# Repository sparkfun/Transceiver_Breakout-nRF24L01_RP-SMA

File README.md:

SparkFun Transceiver Breakout - nRF24L01+ (RP-SMA)
========================================

[*SparkFun Transceiver Breakout - nRF24L01+ (RP-SMA) (WRL-00705)*](https://www.sparkfun.com/products/705)

This module uses the 2.4GHz transceiver from Nordic Semiconductor, the nRF24L01+. 
This board features a reverse polarized SMA connector for maximum RF range.

Repository Contents
-------------------

* **/Hardware** - Eagle design files (.brd, .sch)
* **/Production** - Production panel files (.brd)

Documentation
--------------
* **[Hookup Guide](https://learn.sparkfun.com/tutorials/nrf24l01-transceiver-hookup-guide)** - Basic hookup guide.
* **[SparkFun Fritzing repo](https://github.com/sparkfun/Fritzing_Parts)** - Fritzing diagrams for SparkFun products.
* **[SparkFun 3D Model repo](https://github.com/sparkfun/3D_Models)** - 3D models of SparkFun products. 

License Information
-------------------
This product is _**open source**_! 

The **hardware** is released under [Creative Commons ShareAlike 4.0 International](https://creativecommons.org/licenses/by-sa/4.0/).

Please use, reuse, and modify these files as you see fit. Please maintain attribution to SparkFun Electronics and release anything derivative under the same license.

Distributed as-is; no warranty is given.

- Your friends at SparkFun.

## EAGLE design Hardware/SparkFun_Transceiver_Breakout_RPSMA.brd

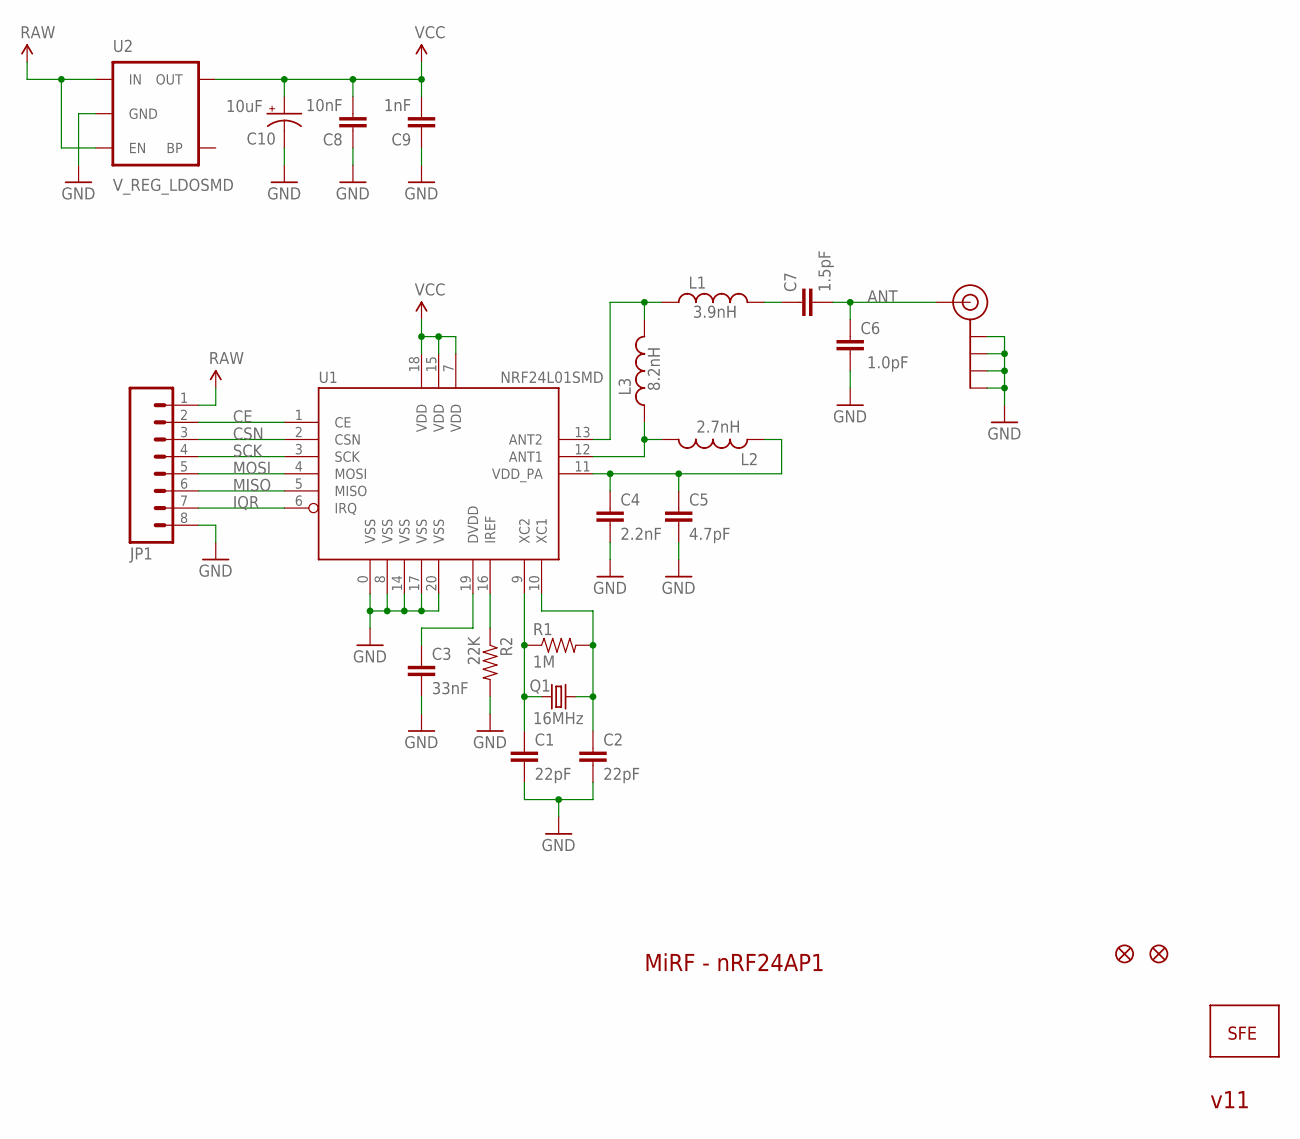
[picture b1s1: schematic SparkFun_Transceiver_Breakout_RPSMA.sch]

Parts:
C1, C2: 22pF; C0402
C3: 33nF; C0402
C4: 2.2nF; C0402
C5: 4.7pF; C0402
C6: 1.0pF; C0402
C7: 1.5pF; C0402
C8: 10nF; C0402
C9: 1nF; C0402
C10: 10uF; EIA3216
FID1, FID2: FIDUCIALUFIDUCIAL; MICRO-FIDUCIAL
J$1: SMA_EDGE; SMA-EDGE
JP1: M08; 1X08
L1: 3.9nH; C0402
L2: 2.7nH; C0402
L3: 8.2nH; C0402
Q1: 16MHz; CRYSTAL-SMD-5X3
R1: 1M; C0402
R2: 22K; C0402
U1: NRF24L01SMD; QFN20
U2: V_REG_LDOSMD; SOT23-5
U$5: LOGO-SFENEW; SFE-NEW-WEBLOGO

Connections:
ANT: C6.2, C7.2, J$1.SIG (SIGNAL)
CE: JP1.2, U1.1 (CE)
CSN: JP1.3, U1.2 (CSN)
GND: C1.2, C2.2, C3.2, C4.2, C5.2, C6.1, C8.1, C9.1, C10.C (-), J$1.GND@0 (GND), J$1.GND@1 (GND), J$1.GND@2 (GND), J$1.GND@3 (GND), JP1.8, R2.2, U1.0 (VSS), U1.8 (VSS), U1.14 (VSS), U1.17 (VSS), U1.20 (VSS), U2.2 (GND)
IQR: JP1.7, U1.6 (IRQ)
MISO: JP1.6, U1.5 (MISO)
MOSI: JP1.5, U1.4 (MOSI)
unnamed: C1.1, Q1.1, R1.1, U1.9 (XC2)
unnamed: C2.1, Q1.3 (2), R1.2, U1.10 (XC1)
unnamed: L2.2, L3.1, U1.12 (ANT1)
unnamed: R2.1, U1.16 (IREF)
unnamed: C3.1, U1.19 (DVDD)
unnamed: L1.1, L3.2, U1.13 (ANT2)
unnamed: C4.1, C5.1, L2.1, U1.11 (VDD_PA)
unnamed: C7.1, L1.2
RAW: JP1.1, U2.1 (IN), U2.3 (EN)
SCK: JP1.4, U1.3 (SCK)
VCC: C8.2, C9.2, C10.A (+), U1.7 (VDD), U1.15 (VDD), U1.18 (VDD), U2.5 (OUT)

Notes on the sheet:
MiRF - nRF24AP1
v11

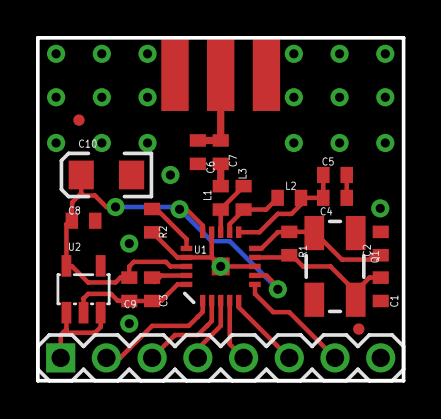
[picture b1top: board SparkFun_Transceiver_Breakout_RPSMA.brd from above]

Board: 2 copper layers, 20.3 x 19.1 mm, 23 parts (1 on the bottom side), 18 nets.

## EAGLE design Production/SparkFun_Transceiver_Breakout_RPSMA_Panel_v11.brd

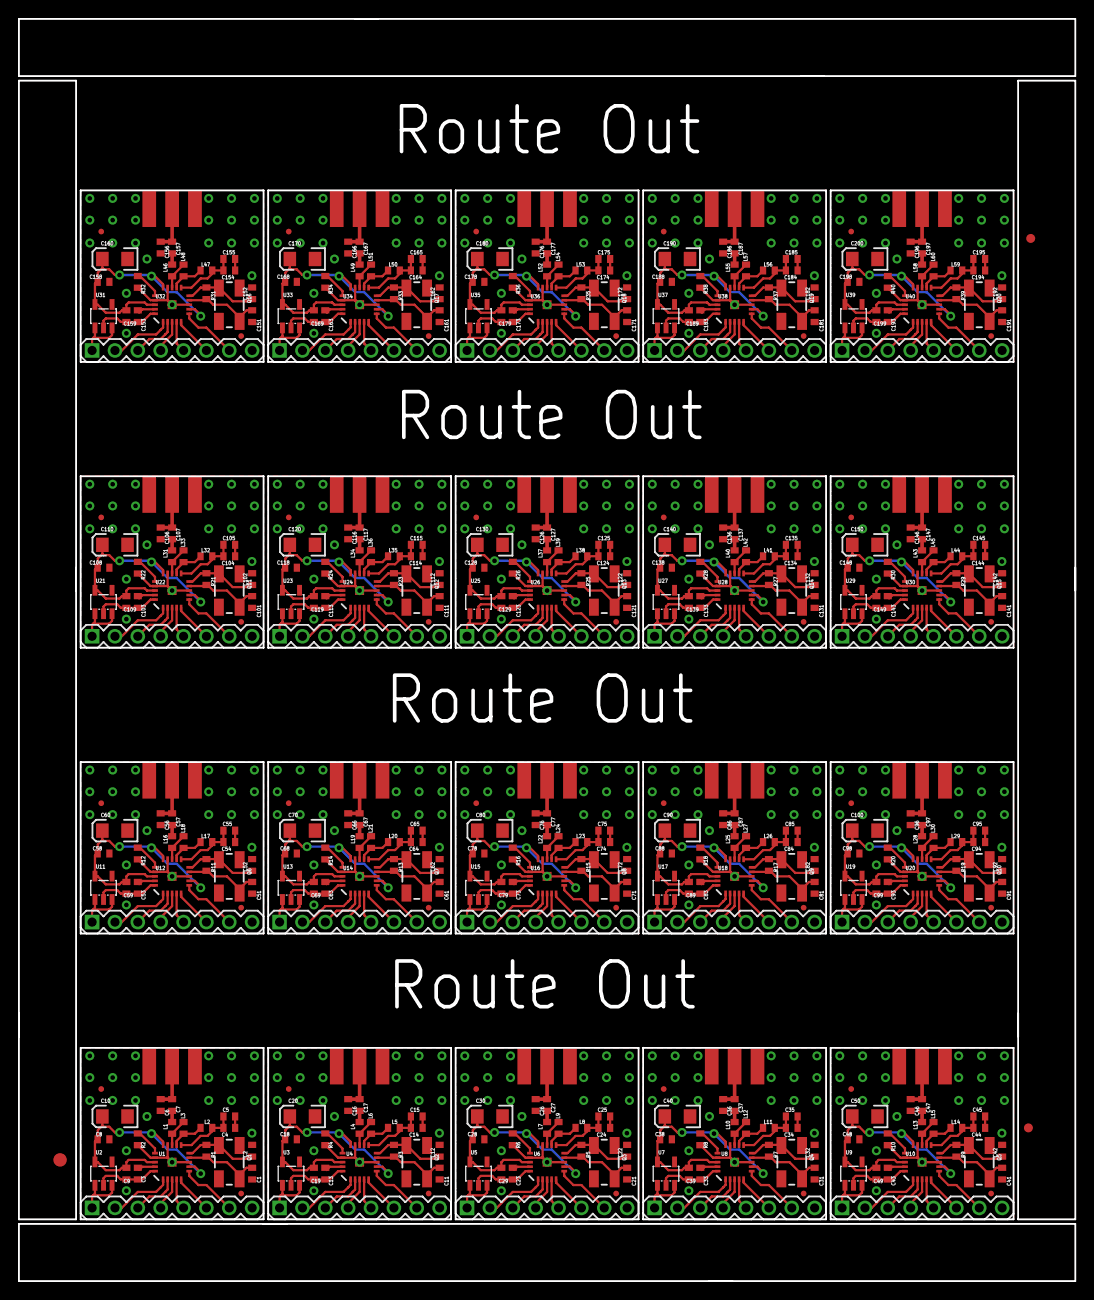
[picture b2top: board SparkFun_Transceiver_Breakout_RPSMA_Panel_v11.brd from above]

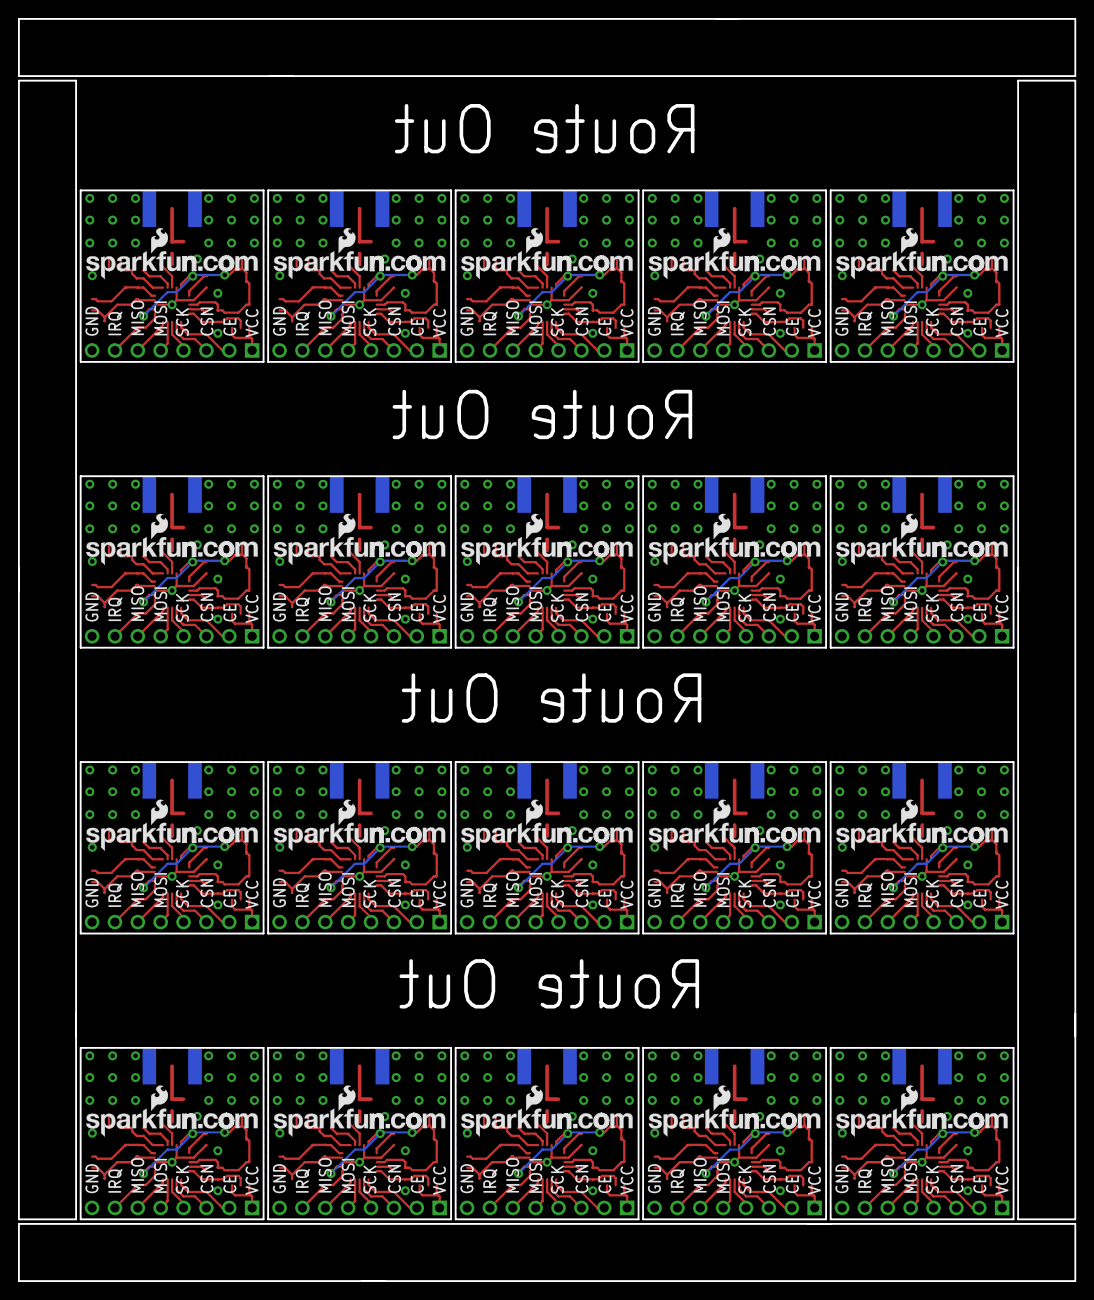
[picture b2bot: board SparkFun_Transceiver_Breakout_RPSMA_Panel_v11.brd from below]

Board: 2 copper layers, 117.3 x 140.2 mm, 463 parts (20 on the bottom side), 360 nets.

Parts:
C1, C2, C11, C12, C21, C22, C31, C32, C41, C42, C51, C52, C61, C62, C71, C72, C81, C82, C91, C92, C101, C102, C111, C112, C121, C122, C131, C132, C141, C142, C151, C152, C161, C162, C171, C172, C181, C182, C191, C192: 22pF; C0402
C3, C13, C23, C33, C43, C53, C63, C73, C83, C93, C103, C113, C123, C133, C143, C153, C163, C173, C183, C193: 33nF; C0402
C4, C14, C24, C34, C44, C54, C64, C74, C84, C94, C104, C114, C124, C134, C144, C154, C164, C174, C184, C194: 2.2nF; C0402
C5, C15, C25, C35, C45, C55, C65, C75, C85, C95, C105, C115, C125, C135, C145, C155, C165, C175, C185, C195: 4.7pF; C0402
C6, C16, C26, C36, C46, C56, C66, C76, C86, C96, C106, C116, C126, C136, C146, C156, C166, C176, C186, C196: 1.0pF; C0402
C7, C17, C27, C37, C47, C57, C67, C77, C87, C97, C107, C117, C127, C137, C147, C157, C167, C177, C187, C197: 1.5pF; C0402
C8, C18, C28, C38, C48, C58, C68, C78, C88, C98, C108, C118, C128, C138, C148, C158, C168, C178, C188, C198: 10nF; C0402
C9, C19, C29, C39, C49, C59, C69, C79, C89, C99, C109, C119, C129, C139, C149, C159, C169, C179, C189, C199: 1nF; C0402
C10, C20, C30, C40, C50, C60, C70, C80, C90, C100, C110, C120, C130, C140, C150, C160, C170, C180, C190, C200: 10uF; EIA3216
E$1: FIDUCIAL-1.5X3
E$5, E$6: FIDUCIAL-1X2
FID1, FID2, FID3, FID4, FID5, FID6, FID7, FID8, FID9, FID10, FID11, FID12, FID13, FID14, FID15, FID16, FID17, FID18, FID19, FID20, FID21, FID22, FID23, FID24, FID25, FID26, FID27, FID28, FID29, FID30, FID31, FID32, FID33, FID34, FID35, FID36, FID37, FID38, FID39, FID40: FIDUCIALUFIDUCIAL; MICRO-FIDUCIAL
J$1, J$2, J$3, J$4, J$5, J$6, J$7, J$8, J$9, J$10, J$11, J$12, J$13, J$14, J$15, J$16, J$17, J$18, J$19, J$20: SMA_EDGE; SMA-EDGE
JP1, JP2, JP3, JP4, JP5, JP6, JP7, JP8, JP9, JP10, JP11, JP12, JP13, JP14, JP15, JP16, JP17, JP18, JP19, JP20: 1X08
L1, L4, L7, L10, L13, L16, L19, L22, L25, L28, L31, L34, L37, L40, L43, L46, L49, L52, L55, L58: 3.9nH; C0402
L2, L5, L8, L11, L14, L17, L20, L23, L26, L29, L32, L35, L38, L41, L44, L47, L50, L53, L56, L59: 2.7nH; C0402
L3, L6, L9, L12, L15, L18, L21, L24, L27, L30, L33, L36, L39, L42, L45, L48, L51, L54, L57, L60: 8.2nH; C0402
Q1, Q2, Q3, Q4, Q5, Q6, Q7, Q8, Q9, Q10, Q11, Q12, Q13, Q14, Q15, Q16, Q17, Q18, Q19, Q20: 16MHz; CRYSTAL-SMD-5X3
R1, R3, R5, R7, R9, R11, R13, R15, R17, R19, R21, R23, R25, R27, R29, R31, R33, R35, R37, R39: 1M; C0402
R2, R4, R6, R8, R10, R12, R14, R16, R18, R20, R22, R24, R26, R28, R30, R32, R34, R36, R38, R40: 22K; C0402
U1, U4, U6, U8, U10, U12, U14, U16, U18, U20, U22, U24, U26, U28, U30, U32, U34, U36, U38, U40: NRF24L01SMD; QFN20
U2, U3, U5, U7, U9, U11, U13, U15, U17, U19, U21, U23, U25, U27, U29, U31, U33, U35, U37, U39: V_REG_LDOSMD; SOT23-5
U$1, U$2, U$3, U$4, U$5, U$6, U$7, U$8, U$9, U$10, U$11, U$12, U$13, U$14, U$15, U$16, U$17, U$18, U$19, U$20: LOGO-SFENEW; SFE-NEW-WEBLOGO

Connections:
ANT: C6.2, C7.2, J$1.SIG
ANT1: C16.2, C17.2, J$2.SIG
ANT2: C26.2, C27.2, J$3.SIG
ANT3: C36.2, C37.2, J$4.SIG
ANT4: C46.2, C47.2, J$5.SIG
ANT5: C56.2, C57.2, J$6.SIG
ANT6: C66.2, C67.2, J$7.SIG
ANT7: C76.2, C77.2, J$8.SIG
ANT8: C86.2, C87.2, J$9.SIG
ANT9: C96.2, C97.2, J$10.SIG
ANT10: C106.2, C107.2, J$11.SIG
ANT11: C116.2, C117.2, J$12.SIG
ANT12: C126.2, C127.2, J$13.SIG
ANT13: C136.2, C137.2, J$14.SIG
ANT14: C146.2, C147.2, J$15.SIG
ANT15: C156.2, C157.2, J$16.SIG
ANT16: C166.2, C167.2, J$17.SIG
ANT17: C176.2, C177.2, J$18.SIG
ANT18: C186.2, C187.2, J$19.SIG
ANT19: C196.2, C197.2, J$20.SIG
CE: JP1.2, U1.1
CE1: JP2.2, U4.1
CE2: JP3.2, U6.1
CE3: JP4.2, U8.1
CE4: JP5.2, U10.1
CE5: JP6.2, U12.1
CE6: JP7.2, U14.1
CE7: JP8.2, U16.1
CE8: JP9.2, U18.1
CE9: JP10.2, U20.1
CE10: JP11.2, U22.1
CE11: JP12.2, U24.1
CE12: JP13.2, U26.1
CE13: JP14.2, U28.1
CE14: JP15.2, U30.1
CE15: JP16.2, U32.1
CE16: JP17.2, U34.1
CE17: JP18.2, U36.1
CE18: JP19.2, U38.1
CE19: JP20.2, U40.1
CSN: JP1.3, U1.2
CSN1: JP2.3, U4.2
CSN2: JP3.3, U6.2
CSN3: JP4.3, U8.2
CSN4: JP5.3, U10.2
CSN5: JP6.3, U12.2
CSN6: JP7.3, U14.2
CSN7: JP8.3, U16.2
CSN8: JP9.3, U18.2
CSN9: JP10.3, U20.2
CSN10: JP11.3, U22.2
CSN11: JP12.3, U24.2
CSN12: JP13.3, U26.2
CSN13: JP14.3, U28.2
CSN14: JP15.3, U30.2
CSN15: JP16.3, U32.2
CSN16: JP17.3, U34.2
CSN17: JP18.3, U36.2
CSN18: JP19.3, U38.2
CSN19: JP20.3, U40.2
GND: C1.2, C2.2, C3.2, C4.2, C5.2, C6.1, C8.1, C9.1, C10.C, J$1.GND@0, J$1.GND@1, J$1.GND@2, J$1.GND@3, JP1.8, R2.2, U1.0, U1.8, U1.14, U1.17, U1.20, U2.2
GND1: C11.2, C12.2, C13.2, C14.2, C15.2, C16.1, C18.1, C19.1, C20.C, J$2.GND@0, J$2.GND@1, J$2.GND@2, J$2.GND@3, JP2.8, R4.2, U3.2, U4.0, U4.8, U4.14, U4.17, U4.20
GND2: C21.2, C22.2, C23.2, C24.2, C25.2, C26.1, C28.1, C29.1, C30.C, J$3.GND@0, J$3.GND@1, J$3.GND@2, J$3.GND@3, JP3.8, R6.2, U5.2, U6.0, U6.8, U6.14, U6.17, U6.20
GND3: C31.2, C32.2, C33.2, C34.2, C35.2, C36.1, C38.1, C39.1, C40.C, J$4.GND@0, J$4.GND@1, J$4.GND@2, J$4.GND@3, JP4.8, R8.2, U7.2, U8.0, U8.8, U8.14, U8.17, U8.20
GND4: C41.2, C42.2, C43.2, C44.2, C45.2, C46.1, C48.1, C49.1, C50.C, J$5.GND@0, J$5.GND@1, J$5.GND@2, J$5.GND@3, JP5.8, R10.2, U9.2, U10.0, U10.8, U10.14, U10.17, U10.20
GND5: C51.2, C52.2, C53.2, C54.2, C55.2, C56.1, C58.1, C59.1, C60.C, J$6.GND@0, J$6.GND@1, J$6.GND@2, J$6.GND@3, JP6.8, R12.2, U11.2, U12.0, U12.8, U12.14, U12.17, U12.20
GND6: C61.2, C62.2, C63.2, C64.2, C65.2, C66.1, C68.1, C69.1, C70.C, J$7.GND@0, J$7.GND@1, J$7.GND@2, J$7.GND@3, JP7.8, R14.2, U13.2, U14.0, U14.8, U14.14, U14.17, U14.20
GND7: C71.2, C72.2, C73.2, C74.2, C75.2, C76.1, C78.1, C79.1, C80.C, J$8.GND@0, J$8.GND@1, J$8.GND@2, J$8.GND@3, JP8.8, R16.2, U15.2, U16.0, U16.8, U16.14, U16.17, U16.20
GND8: C81.2, C82.2, C83.2, C84.2, C85.2, C86.1, C88.1, C89.1, C90.C, J$9.GND@0, J$9.GND@1, J$9.GND@2, J$9.GND@3, JP9.8, R18.2, U17.2, U18.0, U18.8, U18.14, U18.17, U18.20
GND9: C91.2, C92.2, C93.2, C94.2, C95.2, C96.1, C98.1, C99.1, C100.C, J$10.GND@0, J$10.GND@1, J$10.GND@2, J$10.GND@3, JP10.8, R20.2, U19.2, U20.0, U20.8, U20.14, U20.17, U20.20
GND10: C101.2, C102.2, C103.2, C104.2, C105.2, C106.1, C108.1, C109.1, C110.C, J$11.GND@0, J$11.GND@1, J$11.GND@2, J$11.GND@3, JP11.8, R22.2, U21.2, U22.0, U22.8, U22.14, U22.17, U22.20
GND11: C111.2, C112.2, C113.2, C114.2, C115.2, C116.1, C118.1, C119.1, C120.C, J$12.GND@0, J$12.GND@1, J$12.GND@2, J$12.GND@3, JP12.8, R24.2, U23.2, U24.0, U24.8, U24.14, U24.17, U24.20
GND12: C121.2, C122.2, C123.2, C124.2, C125.2, C126.1, C128.1, C129.1, C130.C, J$13.GND@0, J$13.GND@1, J$13.GND@2, J$13.GND@3, JP13.8, R26.2, U25.2, U26.0, U26.8, U26.14, U26.17, U26.20
GND13: C131.2, C132.2, C133.2, C134.2, C135.2, C136.1, C138.1, C139.1, C140.C, J$14.GND@0, J$14.GND@1, J$14.GND@2, J$14.GND@3, JP14.8, R28.2, U27.2, U28.0, U28.8, U28.14, U28.17, U28.20
GND14: C141.2, C142.2, C143.2, C144.2, C145.2, C146.1, C148.1, C149.1, C150.C, J$15.GND@0, J$15.GND@1, J$15.GND@2, J$15.GND@3, JP15.8, R30.2, U29.2, U30.0, U30.8, U30.14, U30.17, U30.20
GND15: C151.2, C152.2, C153.2, C154.2, C155.2, C156.1, C158.1, C159.1, C160.C, J$16.GND@0, J$16.GND@1, J$16.GND@2, J$16.GND@3, JP16.8, R32.2, U31.2, U32.0, U32.8, U32.14, U32.17, U32.20
GND16: C161.2, C162.2, C163.2, C164.2, C165.2, C166.1, C168.1, C169.1, C170.C, J$17.GND@0, J$17.GND@1, J$17.GND@2, J$17.GND@3, JP17.8, R34.2, U33.2, U34.0, U34.8, U34.14, U34.17, U34.20
GND17: C171.2, C172.2, C173.2, C174.2, C175.2, C176.1, C178.1, C179.1, C180.C, J$18.GND@0, J$18.GND@1, J$18.GND@2, J$18.GND@3, JP18.8, R36.2, U35.2, U36.0, U36.8, U36.14, U36.17, U36.20
GND18: C181.2, C182.2, C183.2, C184.2, C185.2, C186.1, C188.1, C189.1, C190.C, J$19.GND@0, J$19.GND@1, J$19.GND@2, J$19.GND@3, JP19.8, R38.2, U37.2, U38.0, U38.8, U38.14, U38.17, U38.20
GND19: C191.2, C192.2, C193.2, C194.2, C195.2, C196.1, C198.1, C199.1, C200.C, J$20.GND@0, J$20.GND@1, J$20.GND@2, J$20.GND@3, JP20.8, R40.2, U39.2, U40.0, U40.8, U40.14, U40.17, U40.20
IQR: JP1.7, U1.6
IQR1: JP2.7, U4.6
IQR2: JP3.7, U6.6
IQR3: JP4.7, U8.6
IQR4: JP5.7, U10.6
IQR5: JP6.7, U12.6
IQR6: JP7.7, U14.6
IQR7: JP8.7, U16.6
IQR8: JP9.7, U18.6
IQR9: JP10.7, U20.6
IQR10: JP11.7, U22.6
IQR11: JP12.7, U24.6
IQR12: JP13.7, U26.6
IQR13: JP14.7, U28.6
IQR14: JP15.7, U30.6
IQR15: JP16.7, U32.6
IQR16: JP17.7, U34.6
IQR17: JP18.7, U36.6
IQR18: JP19.7, U38.6
IQR19: JP20.7, U40.6
MISO: JP1.6, U1.5
MISO1: JP2.6, U4.5
MISO2: JP3.6, U6.5
MISO3: JP4.6, U8.5
MISO4: JP5.6, U10.5
MISO5: JP6.6, U12.5
MISO6: JP7.6, U14.5
MISO7: JP8.6, U16.5
MISO8: JP9.6, U18.5
MISO9: JP10.6, U20.5
MISO10: JP11.6, U22.5
MISO11: JP12.6, U24.5
MISO12: JP13.6, U26.5
MISO13: JP14.6, U28.5
MISO14: JP15.6, U30.5
MISO15: JP16.6, U32.5
MISO16: JP17.6, U34.5
MISO17: JP18.6, U36.5
MISO18: JP19.6, U38.5
MISO19: JP20.6, U40.5
MOSI: JP1.5, U1.4
MOSI1: JP2.5, U4.4
MOSI2: JP3.5, U6.4
MOSI3: JP4.5, U8.4
MOSI4: JP5.5, U10.4
MOSI5: JP6.5, U12.4
MOSI6: JP7.5, U14.4
MOSI7: JP8.5, U16.4
MOSI8: JP9.5, U18.4
MOSI9: JP10.5, U20.4
MOSI10: JP11.5, U22.4
MOSI11: JP12.5, U24.4
MOSI12: JP13.5, U26.4
MOSI13: JP14.5, U28.4
MOSI14: JP15.5, U30.4
MOSI15: JP16.5, U32.4
MOSI16: JP17.5, U34.4
MOSI17: JP18.5, U36.4
MOSI18: JP19.5, U38.4
MOSI19: JP20.5, U40.4
unnamed: C1.1, Q1.1, R1.1, U1.9
unnamed: C2.1, Q1.3, R1.2, U1.10
unnamed: L2.2, L3.1, U1.12
unnamed: R2.1, U1.16
unnamed: C3.1, U1.19
unnamed: L1.1, L3.2, U1.13
unnamed: C4.1, C5.1, L2.1, U1.11
unnamed: C11.1, Q2.1, R3.1, U4.9
unnamed: C7.1, L1.2
unnamed: C12.1, Q2.3, R3.2, U4.10
unnamed: L4.1, L6.2, U4.13
unnamed: C14.1, C15.1, L5.1, U4.11
unnamed: R4.1, U4.16
unnamed: C13.1, U4.19
unnamed: L5.2, L6.1, U4.12
unnamed: C17.1, L4.2
unnamed: C21.1, Q3.1, R5.1, U6.9
unnamed: C22.1, Q3.3, R5.2, U6.10
unnamed: L7.1, L9.2, U6.13
unnamed: C24.1, C25.1, L8.1, U6.11
unnamed: R6.1, U6.16
unnamed: C23.1, U6.19
unnamed: L8.2, L9.1, U6.12
unnamed: C27.1, L7.2
unnamed: C31.1, Q4.1, R7.1, U8.9
unnamed: C32.1, Q4.3, R7.2, U8.10
unnamed: L10.1, L12.2, U8.13
unnamed: C34.1, C35.1, L11.1, U8.11
unnamed: R8.1, U8.16
unnamed: C33.1, U8.19
unnamed: L11.2, L12.1, U8.12
unnamed: C37.1, L10.2
unnamed: C41.1, Q5.1, R9.1, U10.9
unnamed: C42.1, Q5.3, R9.2, U10.10
unnamed: L13.1, L15.2, U10.13
unnamed: C44.1, C45.1, L14.1, U10.11
unnamed: R10.1, U10.16
unnamed: C43.1, U10.19
unnamed: L14.2, L15.1, U10.12
unnamed: C47.1, L13.2
unnamed: C51.1, Q6.1, R11.1, U12.9
unnamed: C52.1, Q6.3, R11.2, U12.10
unnamed: L16.1, L18.2, U12.13
unnamed: C54.1, C55.1, L17.1, U12.11
unnamed: R12.1, U12.16
unnamed: C53.1, U12.19
unnamed: L17.2, L18.1, U12.12
unnamed: C57.1, L16.2
unnamed: C61.1, Q7.1, R13.1, U14.9
unnamed: C62.1, Q7.3, R13.2, U14.10
unnamed: L19.1, L21.2, U14.13
unnamed: C64.1, C65.1, L20.1, U14.11
unnamed: R14.1, U14.16
unnamed: C63.1, U14.19
unnamed: L20.2, L21.1, U14.12
unnamed: C67.1, L19.2
unnamed: C71.1, Q8.1, R15.1, U16.9
unnamed: C72.1, Q8.3, R15.2, U16.10
unnamed: L22.1, L24.2, U16.13
unnamed: C74.1, C75.1, L23.1, U16.11
unnamed: R16.1, U16.16
unnamed: C73.1, U16.19
unnamed: L23.2, L24.1, U16.12
unnamed: C77.1, L22.2
unnamed: C81.1, Q9.1, R17.1, U18.9
unnamed: C82.1, Q9.3, R17.2, U18.10
unnamed: L25.1, L27.2, U18.13
unnamed: C84.1, C85.1, L26.1, U18.11
unnamed: R18.1, U18.16
unnamed: C83.1, U18.19
unnamed: L26.2, L27.1, U18.12
unnamed: C87.1, L25.2
unnamed: C91.1, Q10.1, R19.1, U20.9
unnamed: C92.1, Q10.3, R19.2, U20.10
unnamed: L28.1, L30.2, U20.13
unnamed: C94.1, C95.1, L29.1, U20.11
unnamed: R20.1, U20.16
unnamed: C93.1, U20.19
unnamed: L29.2, L30.1, U20.12
unnamed: C97.1, L28.2
unnamed: C101.1, Q11.1, R21.1, U22.9
unnamed: C102.1, Q11.3, R21.2, U22.10
unnamed: L31.1, L33.2, U22.13
unnamed: C104.1, C105.1, L32.1, U22.11
unnamed: R22.1, U22.16
unnamed: C103.1, U22.19
unnamed: L32.2, L33.1, U22.12
unnamed: C107.1, L31.2
unnamed: C111.1, Q12.1, R23.1, U24.9
unnamed: C112.1, Q12.3, R23.2, U24.10
unnamed: L34.1, L36.2, U24.13
unnamed: C114.1, C115.1, L35.1, U24.11
unnamed: R24.1, U24.16
unnamed: C113.1, U24.19
unnamed: L35.2, L36.1, U24.12
unnamed: C117.1, L34.2
unnamed: C121.1, Q13.1, R25.1, U26.9
unnamed: C122.1, Q13.3, R25.2, U26.10
unnamed: L37.1, L39.2, U26.13
unnamed: C124.1, C125.1, L38.1, U26.11
unnamed: R26.1, U26.16
unnamed: C123.1, U26.19
unnamed: L38.2, L39.1, U26.12
unnamed: C127.1, L37.2
unnamed: C131.1, Q14.1, R27.1, U28.9
unnamed: C132.1, Q14.3, R27.2, U28.10
unnamed: L40.1, L42.2, U28.13
unnamed: C134.1, C135.1, L41.1, U28.11
unnamed: R28.1, U28.16
unnamed: C133.1, U28.19
unnamed: L41.2, L42.1, U28.12
unnamed: C137.1, L40.2
unnamed: C141.1, Q15.1, R29.1, U30.9
unnamed: C142.1, Q15.3, R29.2, U30.10
unnamed: L43.1, L45.2, U30.13
unnamed: C144.1, C145.1, L44.1, U30.11
unnamed: R30.1, U30.16
unnamed: C143.1, U30.19
unnamed: L44.2, L45.1, U30.12
unnamed: C147.1, L43.2
unnamed: C151.1, Q16.1, R31.1, U32.9
unnamed: C152.1, Q16.3, R31.2, U32.10
unnamed: L46.1, L48.2, U32.13
unnamed: C154.1, C155.1, L47.1, U32.11
unnamed: R32.1, U32.16
unnamed: C153.1, U32.19
unnamed: L47.2, L48.1, U32.12
unnamed: C157.1, L46.2
unnamed: C161.1, Q17.1, R33.1, U34.9
unnamed: C162.1, Q17.3, R33.2, U34.10
unnamed: L49.1, L51.2, U34.13
unnamed: C164.1, C165.1, L50.1, U34.11
unnamed: R34.1, U34.16
unnamed: C163.1, U34.19
unnamed: L50.2, L51.1, U34.12
unnamed: C167.1, L49.2
unnamed: C171.1, Q18.1, R35.1, U36.9
unnamed: C172.1, Q18.3, R35.2, U36.10
unnamed: L52.1, L54.2, U36.13
unnamed: C174.1, C175.1, L53.1, U36.11
unnamed: R36.1, U36.16
unnamed: C173.1, U36.19
unnamed: L53.2, L54.1, U36.12
unnamed: C177.1, L52.2
unnamed: C181.1, Q19.1, R37.1, U38.9
unnamed: C182.1, Q19.3, R37.2, U38.10
unnamed: L55.1, L57.2, U38.13
unnamed: C184.1, C185.1, L56.1, U38.11
unnamed: R38.1, U38.16
unnamed: C183.1, U38.19
unnamed: L56.2, L57.1, U38.12
unnamed: C187.1, L55.2
unnamed: C191.1, Q20.1, R39.1, U40.9
unnamed: C192.1, Q20.3, R39.2, U40.10
unnamed: L58.1, L60.2, U40.13
unnamed: C194.1, C195.1, L59.1, U40.11
unnamed: R40.1, U40.16
unnamed: C193.1, U40.19
unnamed: L59.2, L60.1, U40.12
unnamed: C197.1, L58.2
RAW: JP1.1, U2.1, U2.3
RAW1: JP2.1, U3.1, U3.3
RAW2: JP3.1, U5.1, U5.3
RAW3: JP4.1, U7.1, U7.3
RAW4: JP5.1, U9.1, U9.3
RAW5: JP6.1, U11.1, U11.3
RAW6: JP7.1, U13.1, U13.3
RAW7: JP8.1, U15.1, U15.3
RAW8: JP9.1, U17.1, U17.3
RAW9: JP10.1, U19.1, U19.3
RAW10: JP11.1, U21.1, U21.3
RAW11: JP12.1, U23.1, U23.3
RAW12: JP13.1, U25.1, U25.3
RAW13: JP14.1, U27.1, U27.3
RAW14: JP15.1, U29.1, U29.3
RAW15: JP16.1, U31.1, U31.3
RAW16: JP17.1, U33.1, U33.3
RAW17: JP18.1, U35.1, U35.3
RAW18: JP19.1, U37.1, U37.3
RAW19: JP20.1, U39.1, U39.3
SCK: JP1.4, U1.3
SCK1: JP2.4, U4.3
SCK2: JP3.4, U6.3
SCK3: JP4.4, U8.3
SCK4: JP5.4, U10.3
SCK5: JP6.4, U12.3
SCK6: JP7.4, U14.3
SCK7: JP8.4, U16.3
SCK8: JP9.4, U18.3
SCK9: JP10.4, U20.3
SCK10: JP11.4, U22.3
SCK11: JP12.4, U24.3
SCK12: JP13.4, U26.3
SCK13: JP14.4, U28.3
SCK14: JP15.4, U30.3
SCK15: JP16.4, U32.3
SCK16: JP17.4, U34.3
SCK17: JP18.4, U36.3
SCK18: JP19.4, U38.3
SCK19: JP20.4, U40.3
VCC: C8.2, C9.2, C10.A, U1.7, U1.15, U1.18, U2.5
VCC1: C18.2, C19.2, C20.A, U3.5, U4.7, U4.15, U4.18
VCC2: C28.2, C29.2, C30.A, U5.5, U6.7, U6.15, U6.18
VCC3: C38.2, C39.2, C40.A, U7.5, U8.7, U8.15, U8.18
VCC4: C48.2, C49.2, C50.A, U9.5, U10.7, U10.15, U10.18
VCC5: C58.2, C59.2, C60.A, U11.5, U12.7, U12.15, U12.18
VCC6: C68.2, C69.2, C70.A, U13.5, U14.7, U14.15, U14.18
VCC7: C78.2, C79.2, C80.A, U15.5, U16.7, U16.15, U16.18
VCC8: C88.2, C89.2, C90.A, U17.5, U18.7, U18.15, U18.18
VCC9: C98.2, C99.2, C100.A, U19.5, U20.7, U20.15, U20.18
VCC10: C108.2, C109.2, C110.A, U21.5, U22.7, U22.15, U22.18
VCC11: C118.2, C119.2, C120.A, U23.5, U24.7, U24.15, U24.18
VCC12: C128.2, C129.2, C130.A, U25.5, U26.7, U26.15, U26.18
VCC13: C138.2, C139.2, C140.A, U27.5, U28.7, U28.15, U28.18
VCC14: C148.2, C149.2, C150.A, U29.5, U30.7, U30.15, U30.18
VCC15: C158.2, C159.2, C160.A, U31.5, U32.7, U32.15, U32.18
VCC16: C168.2, C169.2, C170.A, U33.5, U34.7, U34.15, U34.18
VCC17: C178.2, C179.2, C180.A, U35.5, U36.7, U36.15, U36.18
VCC18: C188.2, C189.2, C190.A, U37.5, U38.7, U38.15, U38.18
VCC19: C198.2, C199.2, C200.A, U39.5, U40.7, U40.15, U40.18

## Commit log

2015-05-06 Adding hardware files
2015-11-11 added fids to board, created panel

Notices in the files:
parts and their libraries:
SparkFun-Aesthetics: Licensing: Creative Commons ShareAlike 4.0 International - https://creativecommons.org/licenses/by-sa/4.0
